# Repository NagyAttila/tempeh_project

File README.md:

# Autostart on raspberry pi
Add following to ```/etc/rc.local``` :
```screen -dmS auto_tempeh ~root/tempeh_project/screen_start.sh```

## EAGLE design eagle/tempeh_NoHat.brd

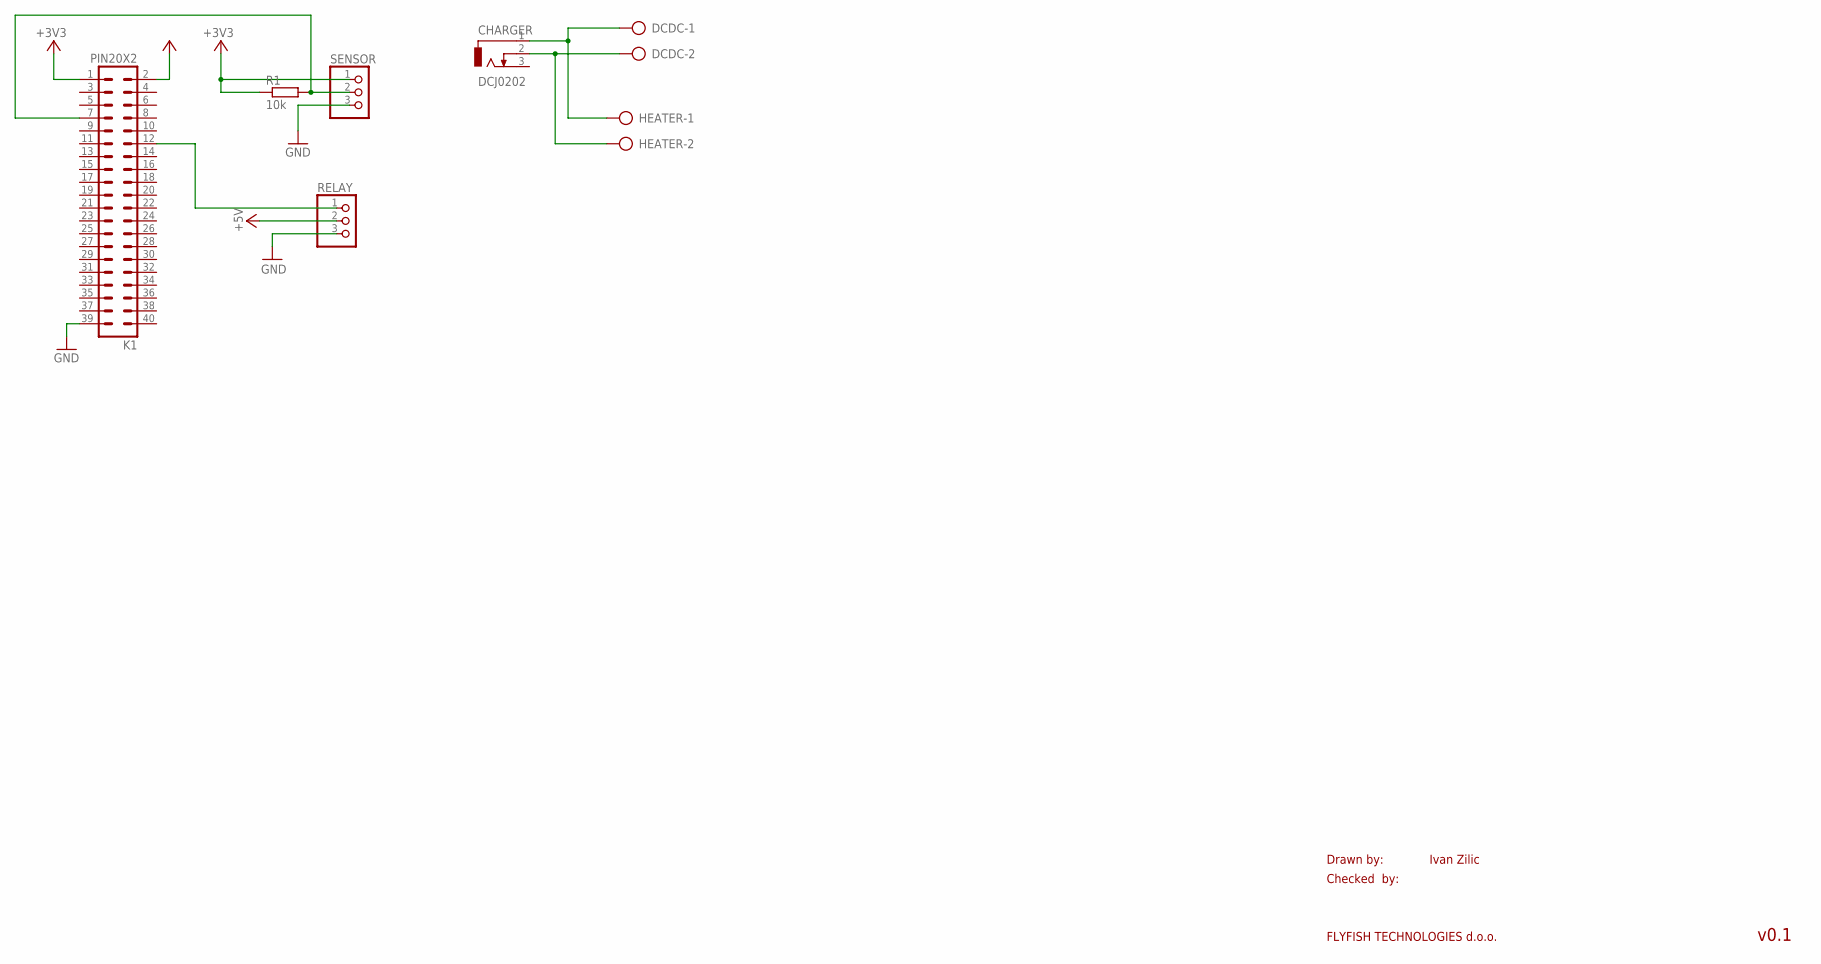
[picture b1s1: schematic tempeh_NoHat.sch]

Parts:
CHARGER: DCJ0202
DCDC: AK300/2
HEATER: AK300/2
K1: PIN20X2; PIN_20X2
R1: 10k; 0204/7
RELAY: PINHD-1X3; 1X03
SENSOR: PINHD-1X3; 1X03

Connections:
+3V3: K1.1, R1.1, SENSOR.1
+5V: K1.2, RELAY.2
GND: K1.39, RELAY.3, SENSOR.3
unnamed: K1.7, R1.2, SENSOR.2
unnamed: K1.12, RELAY.1
unnamed: CHARGER.1, DCDC.1, HEATER.1
unnamed: CHARGER.2, DCDC.2, HEATER.2

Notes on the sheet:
Drawn by:
Checked by:
FLYFISH TECHNOLOGIES d.o.o.
Ivan Zilic
v0.1

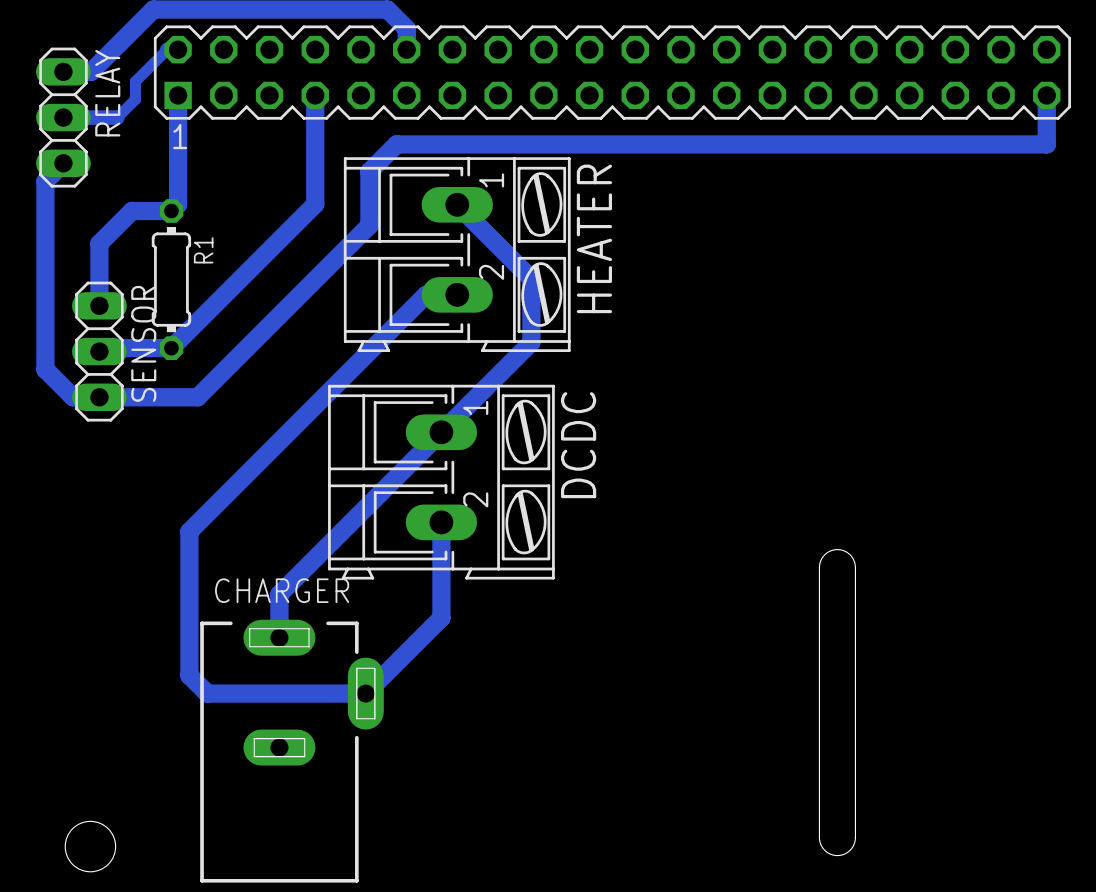
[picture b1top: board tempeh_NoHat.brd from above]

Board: 2 copper layers, 7 parts (0 on the bottom side), 7 nets.

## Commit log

2018-09-14 Adding first working version with simple regulator and DHT11 sensor module.
2018-09-19 adding blinker script
2018-09-19 adding graceful shutdown option to regulator. During graceful shutdown all the GPIO pins are turned off.
2018-10-01 fine tuning
2019-01-26 adding try/catch for sensor data read
2019-07-28 adding schema file and preliminary pcb file of RaspberryPi HAT
2019-07-28 adding pcb v1
2019-08-30 adding NoHat
2019-09-02 new version of pcb board
2020-07-26 adding DHT11 sensor back
2020-07-26 adding Bash test script for DS18B20
2020-07-26 adding possibility to set the measurement period
2020-12-23 add air temp check
2021-03-06 click relay when cables not connected
2021-07-25 remove dht11
2021-08-05 add pwm
